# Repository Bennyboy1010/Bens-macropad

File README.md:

Macro pad for MSFS2024 and other games.

Ignore the code pls. Its taking me a long time to figure out how to code and with the time restrictions I wont be able to finish it in time.

BOM

1x Seeed XIAO RP2040

16x Through-hole 1N4148 Diodes

16x cherry mx keys

4x M3x16mm screws

4x M3 heatset inserts

1x pcb

16x blank dsa caps

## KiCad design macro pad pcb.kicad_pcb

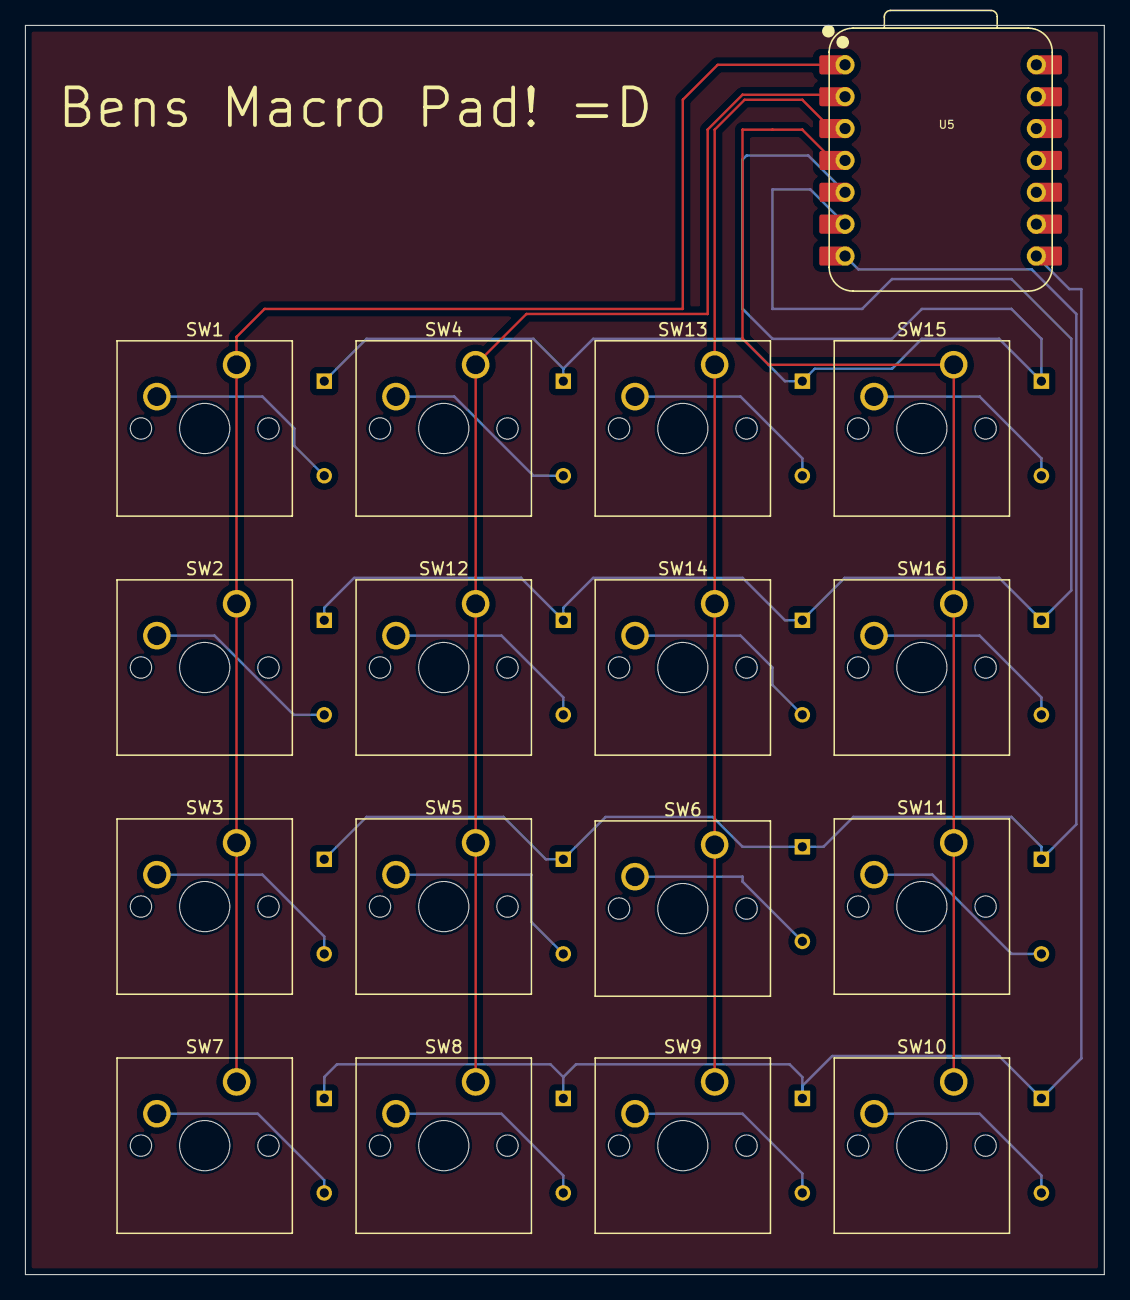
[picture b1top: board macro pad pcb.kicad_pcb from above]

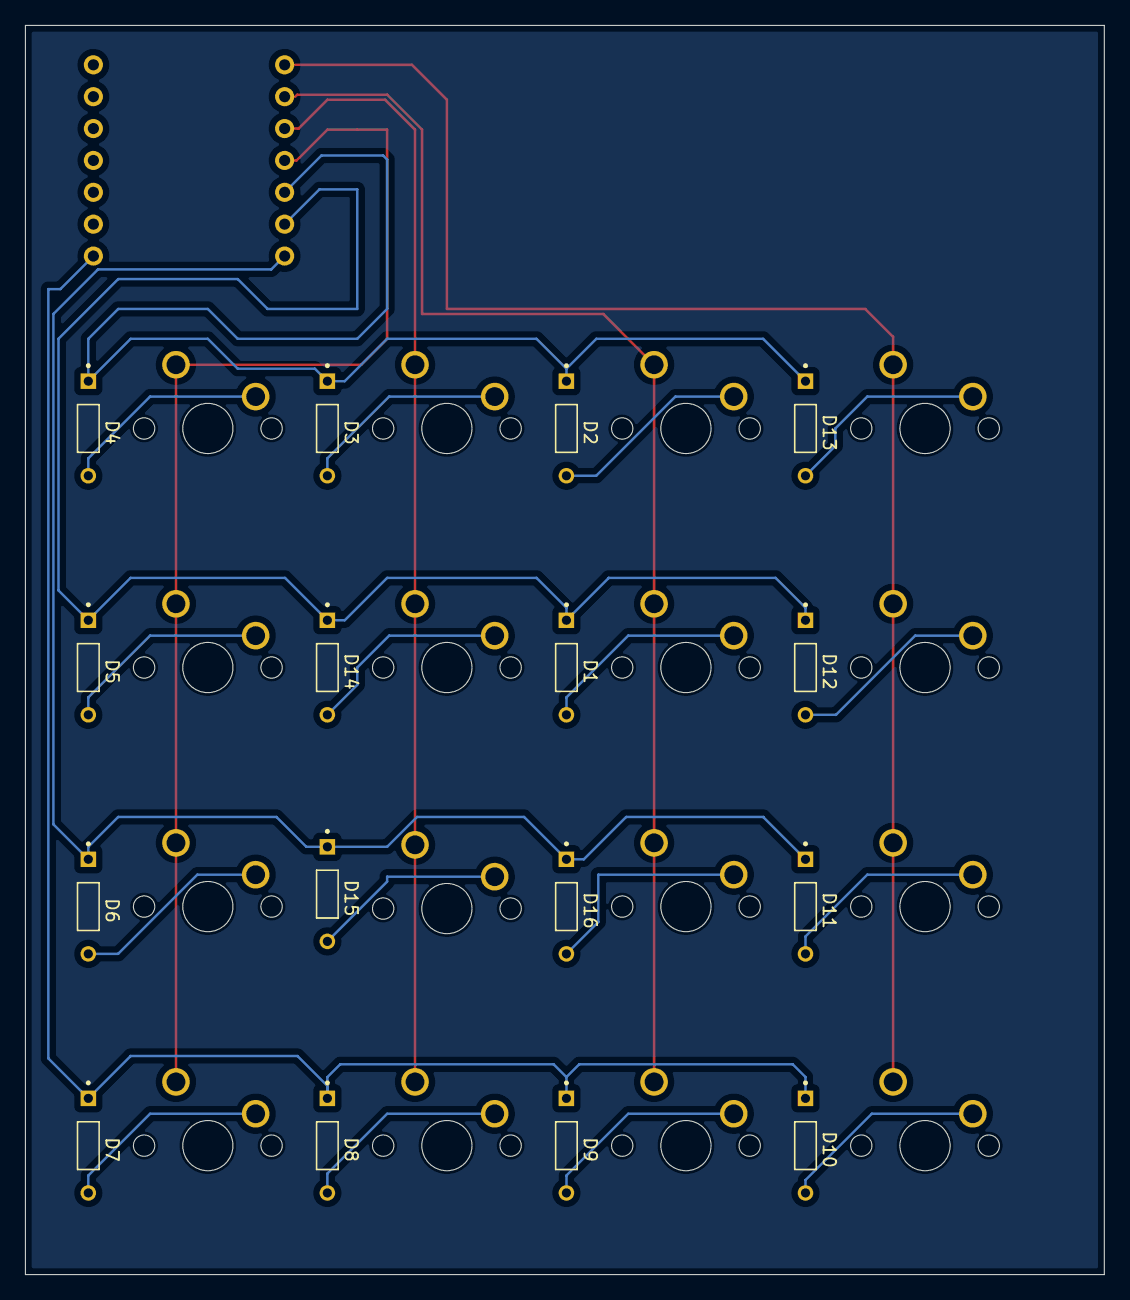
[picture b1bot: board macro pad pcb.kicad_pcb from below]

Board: 2 copper layers, 86.0 x 99.5 mm, 33 parts (16 on the bottom side), 24 nets.

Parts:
D1, D2, D3, D4, D5, D6, D7, D8, D9, D10, D11, D12, D13, D14, D15, D16: 1N4148; DIOAD753W49L380D172B
SW1, SW2, SW3, SW4, SW5, SW6, SW7, SW8, SW9, SW10, SW11, SW12, SW13, SW14, SW15, SW16: SW_Push; SW_Cherry_MX_1.00u_PCB
U5: XIAO-RP2040-DIP

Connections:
unnamed: D1.A, SW12.2
unnamed: D2.A, SW4.2
unnamed: D3.A, SW13.2
unnamed: D4.A, SW15.2
unnamed: D5.A, SW16.2
unnamed: D6.A, SW11.2
unnamed: D7.A, SW10.2
unnamed: D8.A, SW9.2
unnamed: D9.A, SW8.2
unnamed: D10.A, SW7.2
unnamed: D11.A, SW3.2
unnamed: D12.A, SW2.2
unnamed: D13.A, SW1.2
unnamed: D14.A, SW14.2
unnamed: D15.A, SW6.2
unnamed: D16.A, SW5.2
unnamed: D6.K, D11.K, D15.K, D16.K, U5.7 (P0_D6_TX)
unnamed: D7.K, D8.K, D9.K, D10.K, U5.8 (P1_D7_RX)
unnamed: D2.K, D3.K, D4.K, D13.K, U5.5 (P6_SDA_D4)
unnamed: D1.K, D5.K, D12.K, D14.K, U5.6 (P7_SCL_D5)
unnamed: SW1.1, SW2.1, SW3.1, SW7.1, U5.1 (P26_A0_D0)
unnamed: SW4.1, SW5.1, SW8.1, SW12.1, U5.2 (P27_A1_D1)
unnamed: SW6.1, SW9.1, SW13.1, SW14.1, U5.3 (P28_A2_D2)
unnamed: SW10.1, SW11.1, SW15.1, SW16.1, U5.4 (P29_A3_D3)

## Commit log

2025-12-22 Create description
2025-12-22 Update and rename description to description of macro pad
2025-12-24 Create Code for the macro pad
